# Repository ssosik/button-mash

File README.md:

# whack-a-mole-attack

Project files for a two-player whack-a-mole / button mash game

Original idea by https://github.com/DIYTechBros/ButtonSmack / https://www.youtube.com/watch?v=FXypfZi_UDI

Use a Teensy 4 to control the game, sending serial messages to a Matrix Portal for driving the graphics on a 32x32 LED Panel.

The table was built for a Cub Scout pack and plays as **Cub Scout Button Mash**: a medley of
five short games — whack-a-mole, colour finding, a chase around the ring, a colour puzzle,
and Simon — for one or two players. See [Game modes](#game-modes).

This is the second version of the table. The first ran on a resistor-ladder input, plain
dome lamps and a battery pack; its retrospective is at [the end](#version-1-retrospective).
The firmware still builds for both.

# Components

- [Teensy 4.1](https://www.pjrc.com/store/teensy41.html)
- [32x32 Adafruit LED Matrix](https://www.adafruit.com/product/2026)
- [Adafruit Matrix Portal S3](https://www.adafruit.com/product/5778)
- USB-C power bank + an HUSB238 PD trigger board configured for 5 V
  - Replaces the 2× 21700 pack and the XL4015 buck converter, both now removed from the
    design. The pack ran 8.4 V down to 6.0 V, below the XL4015's 8 V input floor for most
    of a discharge; once the current budget was corrected the table turned out to fit
    inside a 5 V / 3 A PD contract, so the converter went away rather than being worked
    around. [The wiring reference](docs/mole-table-wiring.pdf) records the decision, what
    it costs, and how to reverse it.
- 10 60mm dome push-buttons, each with a 12-pixel WS2812 ring in the cap
- 2 arcade buttons (player start)
- 74AHCT125 level shifter for the pixel data line

# Parts

- 73x100mm PCB strip board
- spade terminals + quick connectors
- wire
- connectors
- 330 Ω resistors (one per cap) and a 1000 µF capacitor
- JST-XH connectors and crimp contacts (parts lists in `docs/`)
- 10K resistors and an M/F barrel connector (version 1 only)
- 2x4s
- 1/2 inch finished plywood
- a few 3D printed pieces

# Layout

```
firmware/WhackAMole/   Teensy 4.1 sketch (Arduino/Teensyduino)
firmware/test/         Host-side tests: every game mode, no Teensy needed
display/               CircuitPython for the Matrix Portal S3, plus a host panel tester
docs/                  Wiring reference (HTML source + PDF), parts lists, doc tooling
hardware/              Button bushings (STL), the WS2812 ring carrier (OpenSCAD),
                       and both PCBs, button board and controller (KiCad, generated
                       from Python)
```

Copying `display/` onto the CIRCUITPY drive is most of it, but not all of it —
see [Flashing the Matrix Portal](#flashing-the-matrix-portal).

# Code

The Teensy owns the game. The Matrix Portal renders whatever it is told and holds no
game state of its own.

| File | Role |
| --- | --- |
| `firmware/WhackAMole/Config.h` | Every pin, timing value, and gameplay tunable. Nothing else holds a bare pin number. |
| `firmware/WhackAMole/Protocol.h` | The controller/display wire protocol. Mirrored by `HANDLERS` in `code.py`. |
| `firmware/WhackAMole/WhackAMole.ino` | Wires the hardware objects together and runs the loop. |
| `firmware/WhackAMole/Game.cpp` | Game states, transitions, and the messages sent for each. Runs the medley. |
| `firmware/WhackAMole/Mode.h` | `MODE_LIST`: every way to play, in order, with its banner and segment length. |
| `firmware/WhackAMole/Dance.cpp` | The splash screen's lamp dance: colours spinning round each ring, all caps flashing, alternate caps swapping. Timing in `Config.h`. |
| `firmware/WhackAMole/*Mode.cpp` | One file per mode: Whack, Captcha, Chase, Logic, Simon. See [Game modes](#game-modes). |
| `firmware/WhackAMole/Player.cpp` | One player's buttons, lamps and score. What a press *means* lives in the modes. |
| `firmware/WhackAMole/ButtonInput.cpp` | Buttons, with debounce and edge detection. Analog ladder or one GPIO per button. |
| `firmware/WhackAMole/Lights.cpp` | Button lamps. Plain on/off or WS2812 pixels. |
| `firmware/WhackAMole/Debug.cpp` | Hardware test screens. See below. |
| `display/code.py` | Listens on the UART and drives the panel. |
| `display/boot.py` | Decides whether the game or the host computer owns writes to CIRCUITPY. |
| `firmware/test/` | Host-side tests that play every mode. `make test`; no Teensy needed. |

Input and lamp hardware are selected at build time in `Config.h`:

```c
#define WAM_INPUT_GPIO    1   // 0 = analog resistor ladder, 1 = one GPIO per button
#define WAM_LIGHTS_PIXELS 1   // 0 = digital dome lamps,     1 = WS2812 in the caps
```

Both default to 1, the current table. For version 1's wiring, override them without
editing the file: `make upload GPIO=0 PIXELS=0`.
CI compiles all four combinations so neither path rots.

# Building

Needs `arduino-cli` with the Teensy core:

```sh
brew install arduino-cli
arduino-cli core install teensy:avr \
  --additional-urls https://www.pjrc.com/teensy/package_teensy_index.json
```

Then:

```sh
make build                    # compile the configuration selected in Config.h
make matrix                   # compile all four input/lamp combinations
make upload                   # compile and flash a connected Teensy
make lint                     # clang-format check + ruff + pin-table check
make test                     # play every game mode on this computer; no Teensy needed
```

# Flashing the Matrix Portal

The Portal runs CircuitPython, so this is three separate things: the interpreter,
one library, and the files in `display/`.

**Unplug the 5 V pigtail from the Portal's USB-C before connecting a computer.**
That port is both its power inlet and its data port, and its screw terminals are fed
from the same node. Adafruit warns that two sources on it at once can damage the board.

## 1. CircuitPython

Double-tap **RESET**; a bootloader drive appears. Drag the UF2 for this board onto it
from [circuitpython.org](https://circuitpython.org/board/adafruit_matrixportal_s3/).
It reboots as `CIRCUITPY`.

`code.py` uses `display.root_group`, so it needs **CircuitPython 9 or later**; 10.x is what it is developed against. Nothing in it
needs porting for 10.

## 2. The one library

`code.py` imports `adafruit_display_text`, which is neither built in nor in this repo.
Everything else it imports — `board`, `busio`, `displayio`, `framebufferio`,
`rgbmatrix`, `terminalio`, `storage`, `digitalio` — is already in the UF2.

```sh
uv tool install circup         # or: pipx install circup
circup install adafruit_display_text
```

A bare `pip install circup` fails on a Homebrew Python with
`externally-managed-environment`. Install it as a *tool*, not into this repo — a
virtualenv created inside `display/` drops a `.gitignore` containing `*`, which
silently hides every file in that directory from git, `code.py` included.

`circup` matches the bundle to the installed CircuitPython. By hand works too: copy
`adafruit_display_text/` out of the bundle for your major version into `CIRCUITPY/lib/`.
A bundle from the wrong major version fails at import with *incompatible .mpy file*.

## 3. The files

Both go in the **root** of `CIRCUITPY`.

```sh
cp display/code.py display/boot.py /Volumes/CIRCUITPY/
```

The splash is drawn in code, so there is no image to copy. A `running-monty-mole.bmp`
left on the drive from an older version is unused and can be deleted.

Copy `boot.py` last. On the next reset it calls `storage.remount("/", readonly=False)`,
which hands writes to the program and makes the drive **read-only to your computer**.
That is the point — it is what lets `highscore.txt` persist — but it does mean you
cannot drag files any more.

**To edit the drive again, hold the UP button while powering on.** If you are already
locked out, Ctrl-C into the REPL and run `import storage; storage.remount("/", readonly=True)`.

## Checking it

On reset, before any serial traffic, `code.py` shows the splash: **CUB SCOUT BUTTON
MASH**, one word at a time in two columns, green for P1 and pink for P2, over a spinning
rainbow pinwheel. That
proves CircuitPython, the library, the HUB75 wiring and the panel, with the Teensy not
involved. The splash gives way as soon as the Teensy sends anything, and
comes back each time the attract loop asks for it. The words, timings, pinwheel and the
small font the title is drawn in (needed because `BUTTON` is too long for the built-in
one) are at the top of `code.py`.

Meanwhile every cap lights white as soon as the Teensy boots, which draws enough to keep a
USB power bank from switching itself off. The caps go dark when the attract loop starts,
and then dance during its splash screen.

The handshake is Teensy-driven: it sends `#CONREADY` and waits in `DisplayReadyWait`,
and the Portal answers `#DSPREADY`. A panel that stays on the splash while the Teensy never advances
is a serial-link fault — check the TX/RX crossover first. Once they are talking, the
debug `DISPLAY` screen sends every protocol message in turn.

## When the panel itself is wrong

`display/panel-test.py` runs on the host, not the board, and drives the panel
directly over the CircuitPython REPL — one pattern at a time, naming each one and
then waiting for you, so what is on the panel and what is on screen cannot drift
apart. Each step states what you should see and what a deviation means.

```sh
python3 display/panel-test.py                # step through all fourteen
python3 display/panel-test.py --hold green   # hold one, hands free for probing
python3 display/panel-test.py --list         # names for --hold / --only
```

The order is deliberate: whether the panel blanks on command at all, then which
colour channels light at a current too low for the supply to matter, then the same
at full current, then geometry. A fault at a dim step is not a power problem; one
that appears only at full white is.

`--hold` is the one to reach for with a meter or a loose connector — it parks a
pattern indefinitely while you reseat the HUB75 socket or probe the panel's own
power terminals.

It interrupts `code.py` on the way in and soft-reboots on the way out, so the game
comes back by itself. Nothing is written to CIRCUITPY.

# Game modes

A game is a **medley**: every mode runs in turn, both players at once, each for its own
segment, with a banner between them. Score carries across all of them and the higher total
wins. The order and segment lengths are `MODE_LIST` in `Mode.h`; everything each mode does
inside its segment is tuned in `Config.h`.

| Mode | Banner | What you do |
| --- | --- | --- |
| Whack | `WHACK` | The original game. One cap blinks; hit it before it moves on. |
| Captcha | `FIND` | Your score turns a colour. Every cap shows a different colour, reshuffling; press the one that matches. |
| Chase | `CHASE` | Every cap dim white, one magenta runner circling. Hit the cap it's on — or the next one, just before it lands. Speeds up with each hit. |
| Logic | `LOGIC` | Each press steps a cap to its next colour. Get all five to the colour your score is showing. |
| Simon | `SIMON` | Watch the sequence, play it back. Right, and it grows by one; wrong or too slow, and it replays. |

Two things to check on the real table:

- **`kChasePath`** in `Config.h` is the order of the caps around each player's ring. It
  defaults to button-index order; set it to the real clockwise order or the runner will jump
  around rather than circle. The build refuses a list that skips or repeats a cap.
- **Point values are first guesses.** `make test` holds every mode with a wrong button to one
  rule — mashing at random loses points on average — but how the modes weigh against each
  other needs real players.

Adding a mode is a line in `MODE_LIST` and a class in `Mode.h`. Forgetting the class is a
compile error, and `make test` fails if its banner won't fit on the panel unscrolled.

# Debug mode

Hold **both start buttons together for two seconds** during the attract loop. Everything
reports to USB serial and mirrors a short banner onto the LED matrix, so the table can be
tested standing up with nothing plugged into it.

A lone start press waits `kStartArbitrationMs` (300 ms) before it starts a game, so the
second button has time to arrive. Without that the first press leaves attract mode
immediately and this gesture can never complete — which is exactly what happened once the
Matrix Portal began answering the handshake and the Teensy stopped sitting in
`DisplayReadyWait`, where nothing competes for the press.

- **P1 start** — next screen
- **P2 start** — act within the current screen
- **both held** — leave debug mode

| Screen | What it is for |
| --- | --- |
| LED WALK | Lights each cap in turn and names it. A cap that stays dark is a wiring fault. |
| LED ALL | Everything on solid. Sit here with a meter on the 5 V rail. |
| BUTTONS | The panel shows the held button, still: `P1 B1`–`P1 B5` in wiring order (blue, red, white, green, yellow), `P2 ST` for P2's start, `NONE` when nothing is down. Serial logs live raw values and colour names for both players. |
| CALIBRATE | Walks you through pressing every button, then prints a paste-ready `kLadderThresholds` table and a safe tolerance. Not needed once the buttons are on GPIOs. |
| DISPLAY | Sends every protocol message in turn so `code.py` can be checked against the full vocabulary without playing a round. |

# Circuit

- **[docs/mole-table-wiring.pdf](docs/mole-table-wiring.pdf)** — the full wiring
  reference: power topology and current budget, the controller stripboard, the button
  board, the per-cap connectors, and build order. `docs/wiring.html` is its source;
  `make wiring-pdf` rebuilds it.
- **[hardware/button-board/](hardware/button-board/)** — the button board as a KiCad PCB,
  with its schematic as a [PDF](hardware/button-board/button-board.pdf).

The button board, rendered from the KiCad layout (`make board-render`). Each cap plugs
into one of J1–J10 and each start button into J11 or J12. Power arrives at the J14 screw
terminal, and J13 carries every switch line and the pixel data back to the controller.

- **[hardware/controller-board/](hardware/controller-board/)** — the controller
  stripboard as a PCB: the socketed Teensy, the 74AHCT125, the harness header, the serial
  link to the Portal and the power terminal, with its schematic as a
  [PDF](hardware/controller-board/controller-board.pdf). Generated end to end from a
  netlist that reads `Config.h`; `make controller-board` rebuilds it and holds it to ERC,
  DRC and schematic parity. Not yet fabricated — the stripboard is what is in the table.

## Pin map

Authoritative version is `firmware/WhackAMole/Config.h`; `make check-pins` fails if the
wiring reference disagrees with it.

| Function | Pins |
| --- | --- |
| Display link (Serial1) | 0 (RX), 1 (TX) |
| Reserved for audio | 6, 7, 10, 18, 19, 20, 21, 23 |
| Floating pin, PRNG seed | 17 |
| **Current table** (`WAM_INPUT_GPIO=1`, `WAM_LIGHTS_PIXELS=1`) | |
| Buttons, one GPIO each (B R W G Y, start) | 9, 11, 12, 24, 25, 26 (P1) / 27, 28, 29, 30, 31, 32 (P2) |
| WS2812 data, both players on one chain | 8 |
| **Version 1** (`WAM_INPUT_GPIO=0`, `WAM_LIGHTS_PIXELS=0`) | |
| Analog ladder in | 27 (P1), 38 (P2) |
| Dome lamps | 28–32 (P1), 37–33 (P2) |

The display link was moved off `Serial2`. Pin 7 is `Serial2` RX **and** the I2S data pin
used by both candidate audio designs, so `Serial2` and sound cannot coexist.

# Version 1 retrospective

Written after the first table's first outing. Most of what it asks for is what version 2
became: a 6-pin JST-XH per cap, buttons on their own GPIOs, WS2812 rings in the caps, and
a USB-C power bank in place of the batteries and buck converter.

## What worked well

- The Teensy is an awesome little computer. Easy to code, super fast, really stable, and overall just worked all the time
- Using switches in series with 10K resistors in between is an awesome way to read in multiple distinct user inputs while only using one analog pin
- The serial communication between the teensy and the Portal Matrix worked better than I expected and was more than fast enough
- The physical dome buttons held up well to an hour of constant abuse from a whole pack of Cub Scouts
- The LED Matrix itself was nice and bright and refreshed quickly
- The 21700 batteries and buck converter worked great to power the whole thing (though
  the pack sat below the converter's rated input floor for most of its discharge — see
  the decision record in the wiring reference)

## What I would do different

- The LEDs on the dome buttons are not great, just not bright. The DIY TechBros design replaced the built-in resistor to improve brightness, but it didn't make much of an improvement for me.
- The wiring scheme I came up with worked but it was ugly. If I were going to rewire this, I'd use a 4-pin JST connector and ribbon cable per LED button. The inline resistors would need to be moved to the perf board.
- The analog ladder is clever but it cannot represent two buttons pressed at once — the
  intermediate voltage decodes as some third button. Since a rewire runs a fresh connector
  to every cap anyway, one more conductor per button buys real simultaneous-press handling
  and retires the threshold table entirely.

## Improvements

- SOUNDS! There is an audio break-out board for the Teensy, adding some sounds would really make the game have an arcade feel
- Better button LEDs. I may try to cram a few WS2812B LEDs into the Dome button housing

## Notes from the rewire

The wiring reference has the details; these are the decisions that shaped it.

- Drive WS2812s with **WS2812Serial**, not Adafruit NeoPixel or FastLED. The bit-banging
  drivers disable interrupts for the length of a frame, which jitters the display link and
  will audibly glitch audio.
- The Teensy 4.1 is 3.3 V logic and WS2812Bs want 0.7×VDD on data. Put a **74AHCT125**
  between the Teensy and the first pixel. This is the usual cause of flaky NeoPixel builds.
- A 330 Ω resistor in series with DIN inside **every** cap, so all ten buttons are
  interchangeable, and 1000 µF across the 5 V rail.
- 10 caps × 12-pixel rings = 120 pixels, **~7.2 A** at full white — far past what the
  supply can give. Only two caps are lit during play, but the debug ALL-ON screen is the
  true worst case, so `kPixelBrightness` is capped at 64/255 (~1.8 A). The two start
  buttons have no lamp and are not in the pixel chain.
- Per-cap connector, 6-pin JST-XH: +5 V, GND, DIN, DOUT, SW, SW-GND. Keep the switch return separate
  from the LED return — a ring at full white puts 720 mA down that ground, and sharing it
  offsets the input the Teensy is reading. The start buttons need two conductors only.
- Full topology, current budget and build order: [docs/mole-table-wiring.pdf](docs/mole-table-wiring.pdf).

## Button LED carrier

`hardware/button-led-carrier.scad` — two printed parts that put a 12-pixel WS2812 ring
behind the dome of the stock 60mm button. The ring seat friction-fits into the plunger
cavity; the bore plug replaces the LED holder in the switch bracket and routes the wires
down the hollow stem, so nothing flexes where the spring can reach it. Measurements and
assembly steps are in the file. The `assert`s at the top will refuse to render if your
ring is too tall for the 4mm cavity — measure `ring_height` before printing.

# Table design

From version 1; the playfield and frame carried over unchanged.

I started from the playfield (16x36 inches) and then just built a table from and legs underneath that. I needed to 3d print a few spacer/bushings so that the buttons were snug in the holes I cut (I didn't have a perfectly-sized hole saw). I also 3d printed 21700 battery holders. The battery holders and perf-board are just screwed to the underside with wood screws. The PortalMatrix is piggy-backed onto the back of the LED panel on the 2x10 socket connector. The LED panel is inset into the middle of the playfield; I added supports underneath to keep it flush with the playfield surface. I also added a 3d-printed bezel around the LED panel in an attempt to make it look like a mole hill and to discourage players from bonking it.

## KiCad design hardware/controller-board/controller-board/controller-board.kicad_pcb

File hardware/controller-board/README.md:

# Controller board

The controller stripboard from [the wiring reference](../../docs/mole-table-wiring.pdf)
— 33 cuts and nine jumpers around a socketed Teensy 4.1 — as a two-layer PCB. Same
parts, same connectors, same pinout: the harness to the button board, the serial cable
to the Matrix Portal and the 5 V lead from the star all plug into it unchanged.

## Files

| File | What |
| --- | --- |
| `gen-netlist.py` | The single source of truth. Harness positions come from the button board's generator and switch pins from `Config.h`, so neither can drift from it. |
| `gen-schematic.py` | Draws the schematic from that netlist, and writes the Teensy 4.1 symbol KiCad does not ship. |
| `gen-pcb.py` | Places, routes and pours the board through KiCad's own `pcbnew` API, and writes the Teensy footprint. |
| `controller-board/` | The KiCad project. Everything in it is generated. |
| `controller-board.pdf` | The schematic as a drawing. |

```sh
make controller-board   # regenerate all of it, then ERC, DRC and schematic parity
make board-render       # the 3D view above
```

`gen-pcb.py` has to run under the Python inside KiCad, the only one that can import
`pcbnew`; the Makefile knows where it is. Unlike the button board, nothing here is
laid out by hand, so regenerating is always safe: edit the generator, never the board.

## What it checks

`make controller-board` fails on any of these, warnings included:

- **ERC** — 0 errors, 0 warnings. Every open pin carries an explicit no-connect.
- **DRC** — 0 violations, 0 unconnected items.
- **Schematic parity** — every footprint is linked to its symbol and every pad
  carries the net the schematic gives it. The links are UUIDs derived from
  reference designators, so the two generators agree without sharing state.

The schematic's exported netlist also diffs clean against `gen-netlist.py` — 18 nets,
53 nodes — and the netlist validator refuses a pin on two nets, a pin on none, a net
with one end, or a disabled '125 output wired to anything.

## Layout

It copies the stripboard on purpose. The harness header sits one column from the
Teensy's left row, so twelve of its fourteen positions are a straight trace to the
Teensy pin opposite — the PCB version of "the strip is the wire". The other two arrive
from elsewhere, exactly as on the stripboard: position 2 is ground, from the pour, and
position 5 is the level-shifted pixel data, run down the board's left edge on the
bottom layer.

| Ref | Part | Notes |
| --- | --- | --- |
| U1 | Teensy 4.1 on two 1×24 female headers | **Cut the VIN–VUSB pad** on the Teensy, or USB and the star will fight. |
| U2 | 74AHCT125 in a DIP-14 socket | Gate 1 lifts pin 8 to 5 V. Gates 2–4 are disabled (OE high), inputs grounded. |
| J1 | 1×14 2.54 mm pin header | Takes the harness's socket end; mates with button board J13. Pin 1 is P1 BLUE. |
| J2 | B3B-XH-A | Serial1 to the Portal: 1 GND, 2 Teensy RX, 3 Teensy TX. The cable crosses 2 and 3. |
| J3 | MX126 screw terminal | +5 V and GND from the star. A screw terminal, as on the button board. |
| C1 | 100 µF / 16 V | Bulk at the power entry. Stripe to GND. |
| C2 | 100 nF ceramic | Decoupling, straight onto the '125's VCC pin. |
| H1–H4 | M3, unplated | Mounting. |

Ground is a pour on both layers. +5 V reaches VIN and C1 on the top layer, and runs
along the top edge on the bottom layer to the '125.

## Before ordering

This has been through every check KiCad offers, but not through a fab or a first
article. Open it in KiCad and look it over before you send it anywhere, and check
the Teensy footprint against a real Teensy and its headers — it is drawn from the
published 0.6" row spacing, not measured from a part.

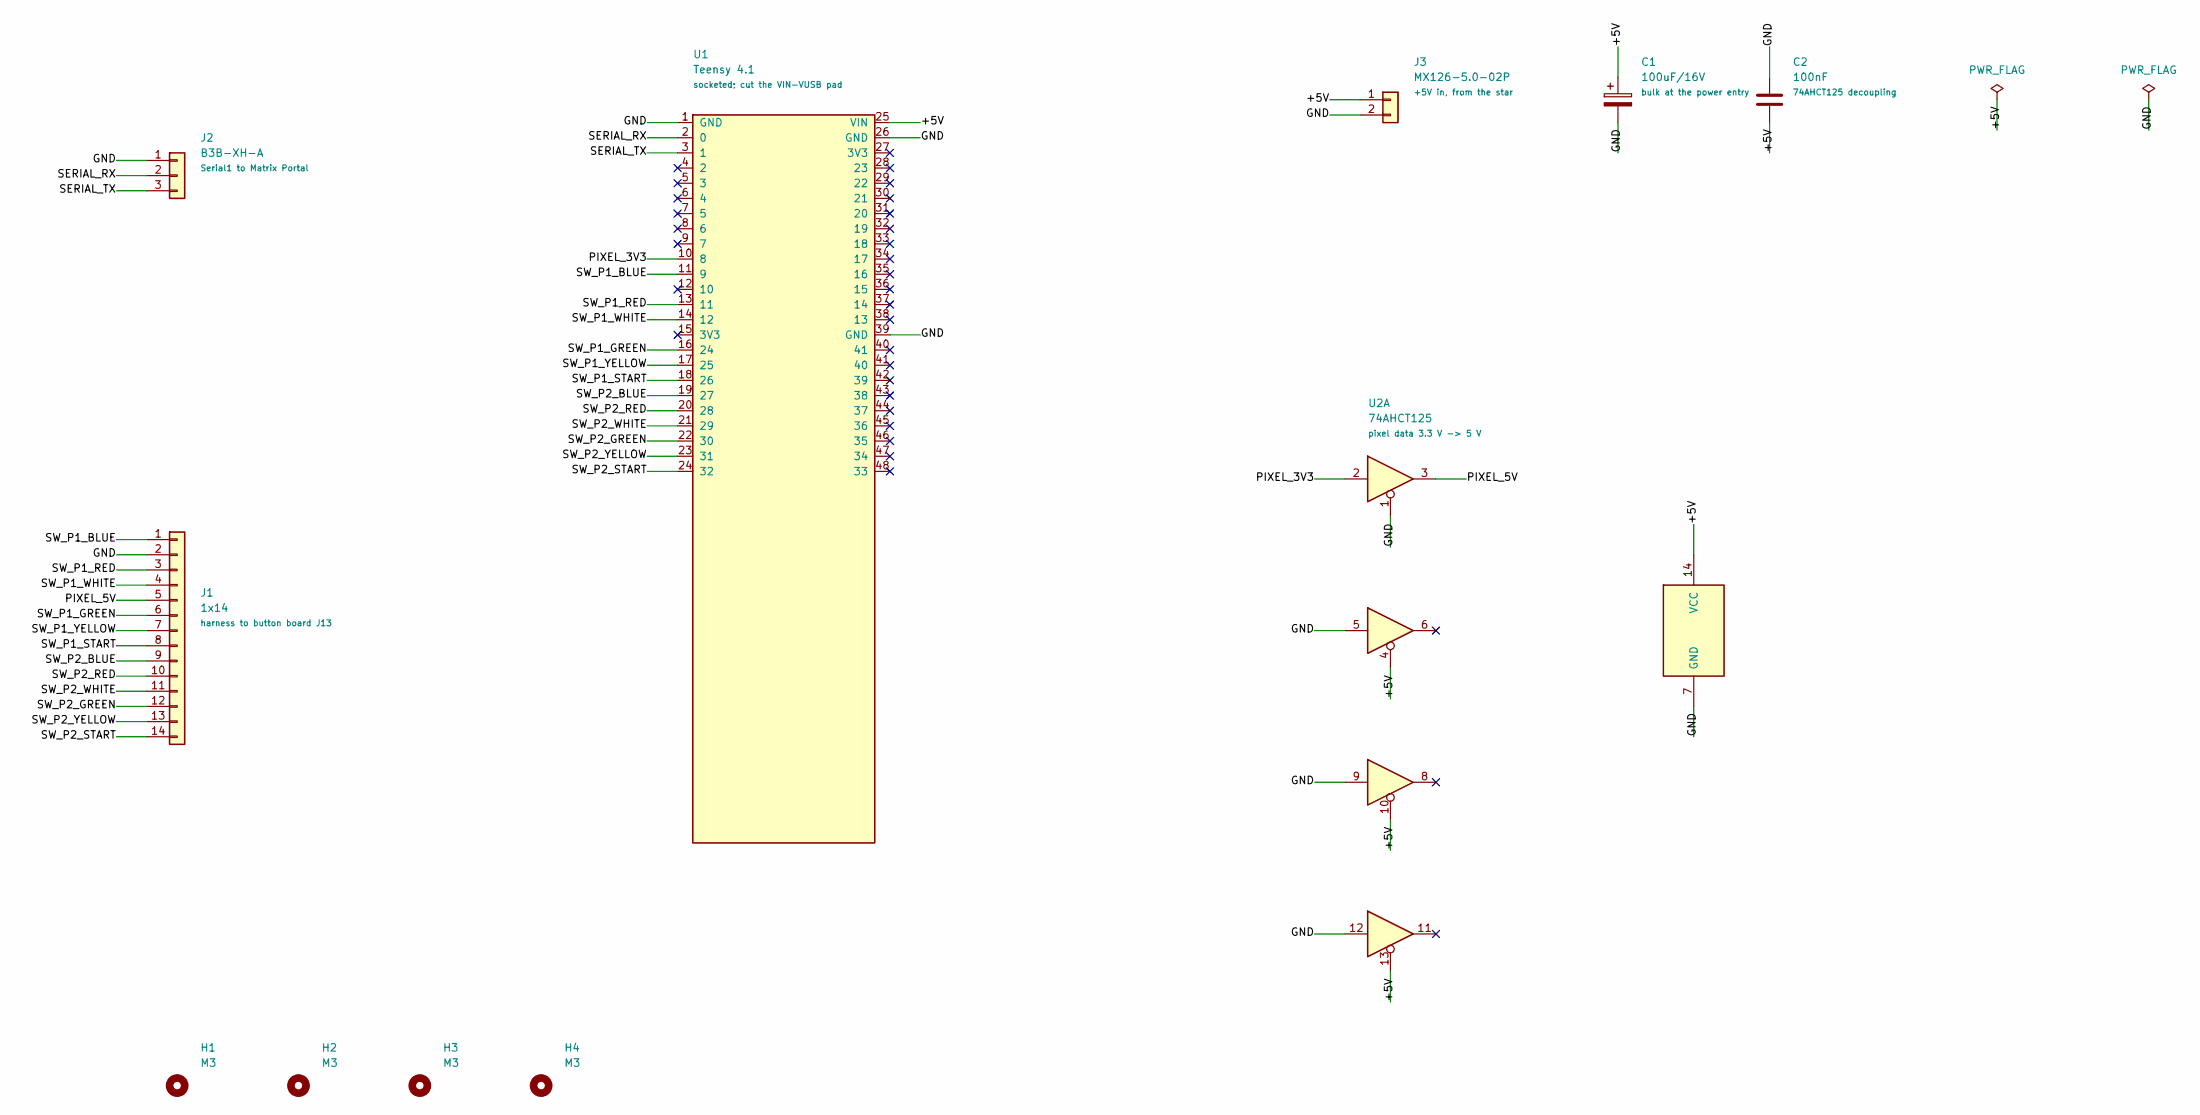
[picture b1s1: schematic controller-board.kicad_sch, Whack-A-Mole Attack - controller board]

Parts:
C1: 100uF/16V; CP_Radial_D6.3mm_P2.50mm
C2: 100nF; C_Disc_D5.0mm_W2.5mm_P5.00mm
H1, H2, H3, H4: M3; MountingHole_3.2mm_M3
J1: 1x14; PinHeader_1x14_P2.54mm_Vertical
J2: B3B-XH-A; JST_XH_B3B-XH-A_1x03_P2.50mm_Vertical
J3: MX126-5.0-02P; TerminalBlock_MaiXu_MX126-5.0-02P_1x02_P5.00mm
U1: Teensy 4.1; Teensy41_Socketed
U2: 74AHCT125; DIP-14_W7.62mm_Socket

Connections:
/+5V: C1.1, C2.2, J3.1, U1.25 (VIN), U2.4, U2.10, U2.13, U2.14 (VCC)
/GND: C1.2, C2.1, J1.2, J2.1, J3.2, U1.1 (GND), U1.26 (GND), U1.39 (GND), U2.1, U2.5, U2.7 (GND), U2.9, U2.12
/PIXEL_3V3: U1.10 (8), U2.2
/PIXEL_5V: J1.5, U2.3
/SERIAL_RX: J2.2, U1.2 (0)
/SERIAL_TX: J2.3, U1.3 (1)
/SW_P1_BLUE: J1.1, U1.11 (9)
/SW_P1_GREEN: J1.6, U1.16 (24)
/SW_P1_RED: J1.3, U1.13 (11)
/SW_P1_START: J1.8, U1.18 (26)
/SW_P1_WHITE: J1.4, U1.14 (12)
/SW_P1_YELLOW: J1.7, U1.17 (25)
/SW_P2_BLUE: J1.9, U1.19 (27)
/SW_P2_GREEN: J1.12, U1.22 (30)
/SW_P2_RED: J1.10, U1.20 (28)
/SW_P2_START: J1.14, U1.24 (32)
/SW_P2_WHITE: J1.11, U1.21 (29)
/SW_P2_YELLOW: J1.13, U1.23 (31)

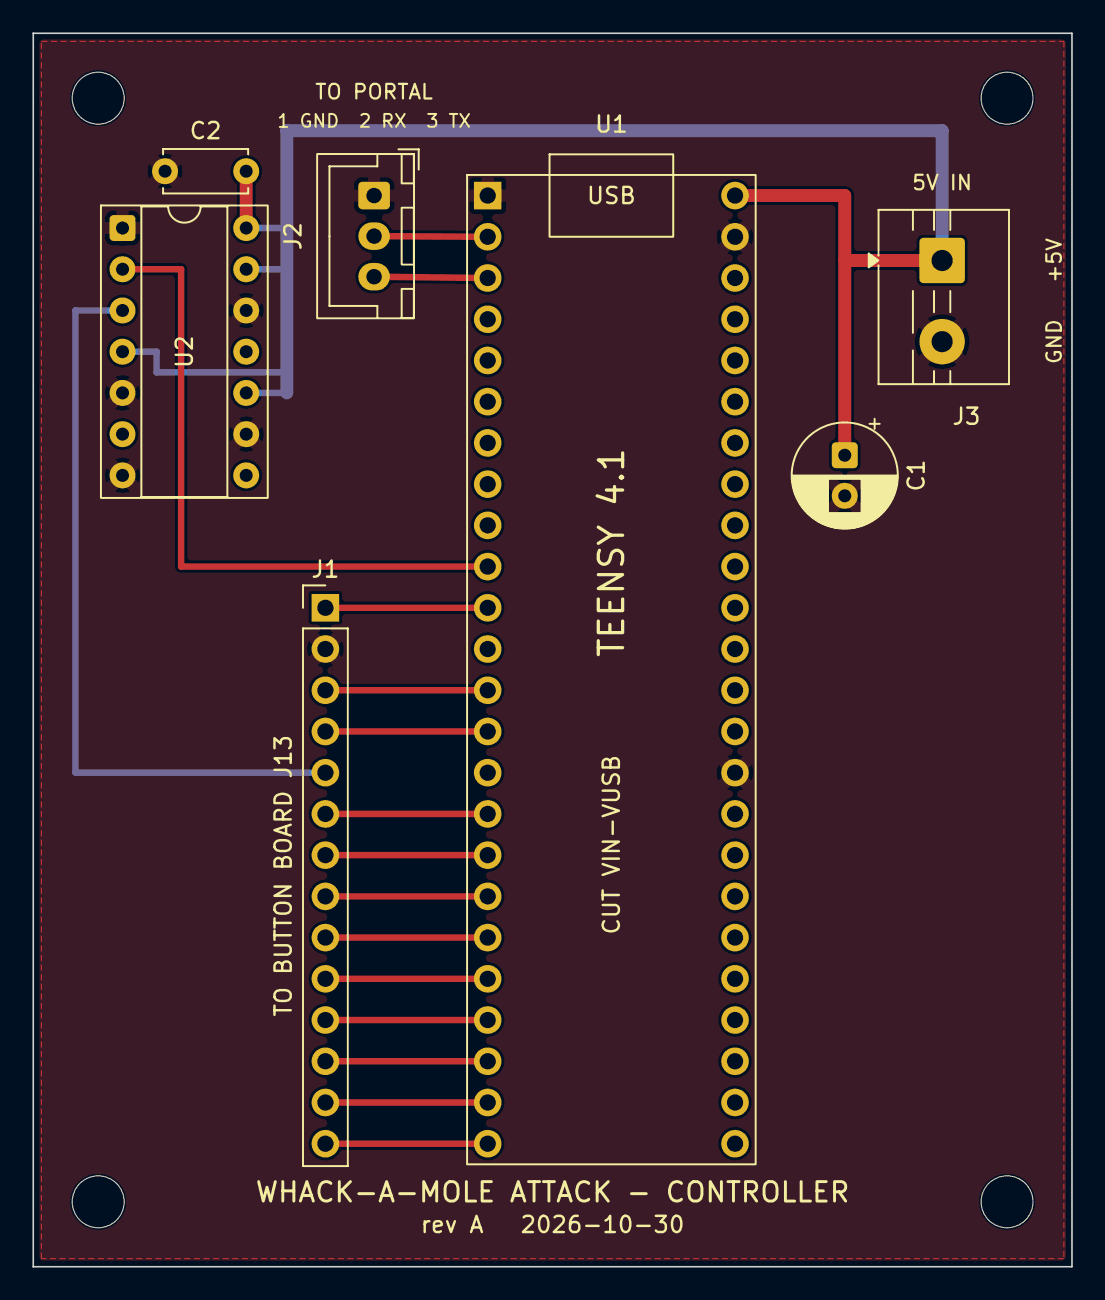
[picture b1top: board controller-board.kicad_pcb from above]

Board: 2 copper layers, 64.0 x 76.0 mm, 11 parts (0 on the bottom side), 18 nets.

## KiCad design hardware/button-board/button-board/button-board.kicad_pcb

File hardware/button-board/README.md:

# Button board

Twelve connectors, three power nets, one daisy chain. The stripboard version is
documented in [the wiring reference](../../docs/mole-table-wiring.pdf) — 63 cuts
and 31 hand-soldered wires. This directory is the PCB alternative.

## Files

| File | What |
| --- | --- |
| `gen-netlist.py` | The single source of truth. Everything else derives from it. |
| `gen-schematic.py` | Draws the schematic from that netlist. |
| `button-board/` | The KiCad project. `button-board.net` and `button-board.kicad_sch` in it are generated; `button-board.kicad_pcb` is laid out by hand. |
| `button-board.pdf` | The schematic as a drawing, for reading away from KiCad. |

```sh
cd hardware/button-board
python3 gen-netlist.py                               # readable net table
python3 gen-netlist.py --kicad > button-board/button-board.net
python3 gen-schematic.py       > button-board/button-board.kicad_sch

# Regenerating the schematic assigns fresh symbol UUIDs, so the board's
# footprint links go stale. Re-import with "Update PCB from Schematic" and
# tick "Re-link footprints to schematic symbols based on their reference
# designators", or the 20 existing footprints come back as orphans.
```

Connections are made with net labels on pin stubs rather than drawn wires. For
twelve connectors and three buses that is the clearer drawing, and it removes
the class of bug where a generated wire lands a fraction off a pin and silently
connects nothing.

Both outputs are checked, not assumed. ERC reports **0 errors, 0 warnings**, and
the schematic is exported back to a netlist and diffed against the hand-built
one — 25 nets and 83 nodes, matching exactly. ERC alone is not sufficient: an
earlier draft passed ERC while connecting nothing at all.

Ribbon positions are read out of `firmware/WhackAMole/Config.h` rather than
written down here, so the netlist cannot drift from the firmware the way the
documentation did three times. The generator also refuses to emit anything if a
connector pin lands on two nets, on none, or does not exist — verified against
injected faults, not only on correct input.

## Designators

`J1`–`J10` are the lit caps **in pixel-chain order**: P1 blue, red, white,
green, yellow, then P2 in the same sequence. That is both the order data flows
and the order `Config.h` addresses them, so the reference designator is the
pixel index. `J11`/`J12` are the start buttons, `J13` the ribbon to the
controller, `J14` power in from the HUSB238.

## The one thing layout must get right

`GND_LED` and `GND_SW` are **separate nets joined only at `NT1`**. That single
point is the star. A ground pour that merges them anywhere else puts up to
1.81 A of ring current through the switch reference, and the symptom is inputs
that misread while the LEDs are busy — intermittent, load-dependent, and
unpleasant to chase. Keep the net tie, and check it survives the pour.

Beyond that: `+5V` and `GND_LED` want wide copper, since they carry the ring
current. Everything else is signal.

## Footprints

Checked against KiCad 10's libraries. Verify them if you are on another release
— JST and pin header library names have moved between versions.

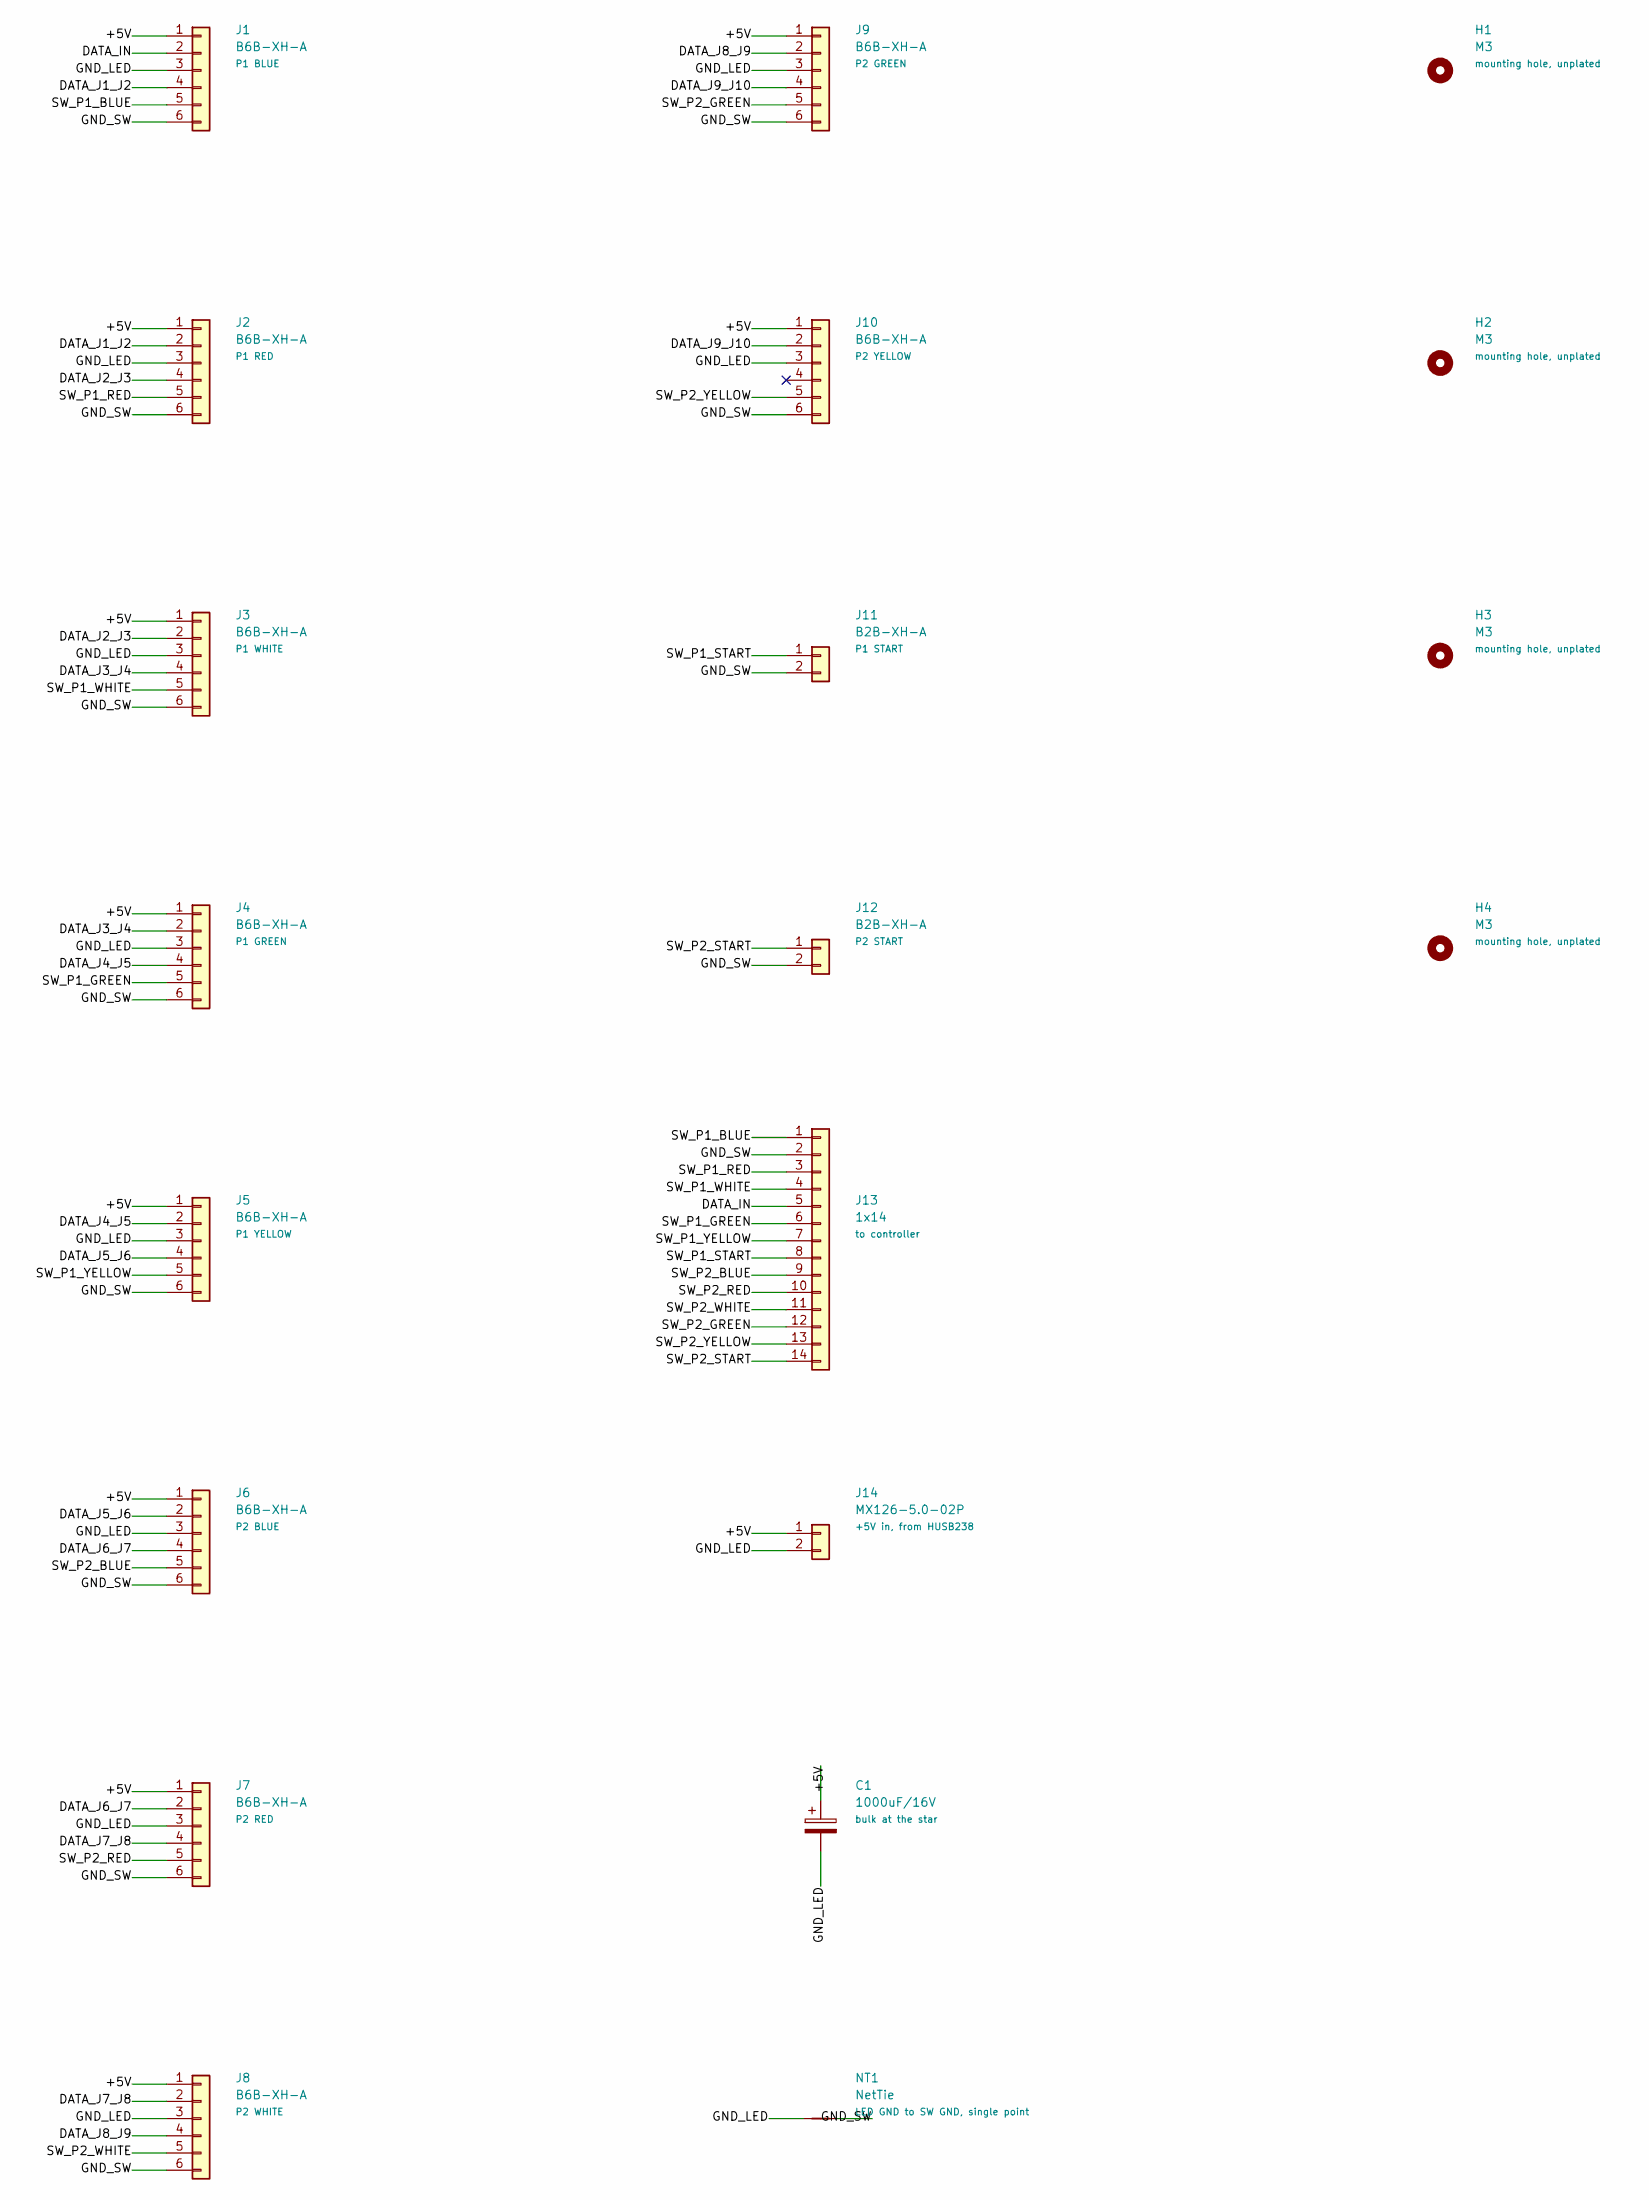
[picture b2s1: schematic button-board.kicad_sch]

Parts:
C1: 1000uF/16V; CP_Radial_D10.0mm_P5.00mm
H1, H2, H3, H4: M3; MountingHole_3.2mm_M3
J1, J2, J3, J4, J5, J6, J7, J8, J9, J10: B6B-XH-A; JST_XH_B6B-XH-A_1x06_P2.50mm_Vertical
J11, J12: B2B-XH-A; JST_XH_B2B-XH-A_1x02_P2.50mm_Vertical
J13: 1x14; JST_XH_B14B-XH-A_1x14_P2.50mm_Vertical
J14: MX126-5.0-02P; TerminalBlock_MaiXu_MX126-5.0-02P_1x02_P5.00mm
NT1: NetTie; NetTie-2_THT_Pad1.0mm

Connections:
/+5V: C1.1, J1.1, J2.1, J3.1, J4.1, J5.1, J6.1, J7.1, J8.1, J9.1, J10.1, J14.1
/DATA_IN: J1.2, J13.5
/DATA_J1_J2: J1.4, J2.2
/DATA_J2_J3: J2.4, J3.2
/DATA_J3_J4: J3.4, J4.2
/DATA_J4_J5: J4.4, J5.2
/DATA_J5_J6: J5.4, J6.2
/DATA_J6_J7: J6.4, J7.2
/DATA_J7_J8: J7.4, J8.2
/DATA_J8_J9: J8.4, J9.2
/DATA_J9_J10: J9.4, J10.2
/GND_LED: C1.2, J1.3, J2.3, J3.3, J4.3, J5.3, J6.3, J7.3, J8.3, J9.3, J10.3, J14.2, NT1.1
/GND_SW: J1.6, J2.6, J3.6, J4.6, J5.6, J6.6, J7.6, J8.6, J9.6, J10.6, J11.2, J12.2, J13.2, NT1.2
/SW_P1_BLUE: J1.5, J13.1
/SW_P1_GREEN: J4.5, J13.6
/SW_P1_RED: J2.5, J13.3
/SW_P1_START: J11.1, J13.8
/SW_P1_WHITE: J3.5, J13.4
/SW_P1_YELLOW: J5.5, J13.7
/SW_P2_BLUE: J6.5, J13.9
/SW_P2_GREEN: J9.5, J13.12
/SW_P2_RED: J7.5, J13.10
/SW_P2_START: J12.1, J13.14
/SW_P2_WHITE: J8.5, J13.11
/SW_P2_YELLOW: J10.5, J13.13

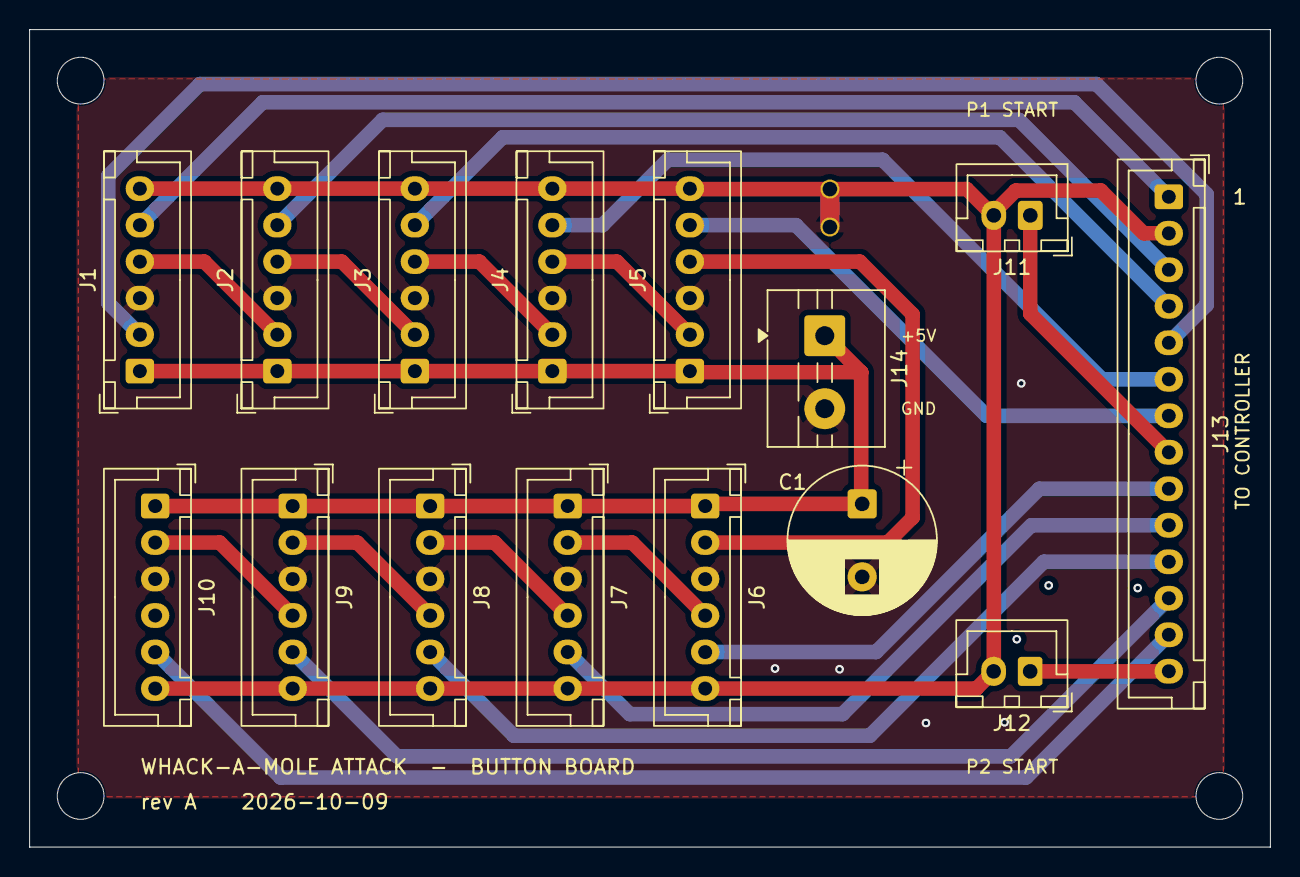
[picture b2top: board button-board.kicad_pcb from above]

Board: 2 copper layers, 85.0 x 56.0 mm, 20 parts (0 on the bottom side), 25 nets.

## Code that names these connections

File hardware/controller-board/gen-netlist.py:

#!/usr/bin/env python3
"""The controller board's netlist: one description the schematic and the PCB
are both generated from, so the two cannot disagree.

It is the stripboard in docs/wiring.html, made as a PCB: a socketed Teensy
4.1, a 74AHCT125 lifting the pixel data to 5 V, the 14-way header for the
harness to the button board, a 3-pin JST-XH serial link to the Matrix Portal,
and a screw terminal for 5 V in from the star.

Nothing here is written down twice. The harness positions come from the
button board's own generator, so both ends of the harness agree by
construction, and the switch pins come from Config.h, so a firmware pin change
that the board does not follow fails here instead of on the table.

    python3 hardware/controller-board/gen-netlist.py    # readable net table
"""

import importlib.util
import pathlib
import sys
from collections import defaultdict

HERE = pathlib.Path(__file__).resolve().parent
_spec = importlib.util.spec_from_file_location(
    "button_netlist", HERE.parent / "button-board" / "gen-netlist.py"
)
BB = importlib.util.module_from_spec(_spec)
_spec.loader.exec_module(BB)

# The Teensy 4.1's two outer pin rows, top view, USB end first. Pads are
# numbered 1-24 down the left row and 25-48 down the right, so pad numbers
# read the way the board is held rather than anticlockwise like a DIP.
TEENSY_LEFT = [
    "GND",
    "0",
    "1",
    "2",
    "3",
    "4",
    "5",
    "6",
    "7",
    "8",
    "9",
    "10",
    "11",
    "12",
    "3V3",
    "24",
    "25",
    "26",
    "27",
    "28",
    "29",
    "30",
    "31",
    "32",
]
TEENSY_RIGHT = [
    "VIN",
    "GND",
    "3V3",
    "23",
    "22",
    "21",
    "20",
    "19",
    "18",
    "17",
    "16",
    "15",
    "14",
    "13",
    "GND",
    "41",
    "40",
    "39",
    "38",
    "37",
    "36",
    "35",
    "34",
    "33",
]
TEENSY_PINS = TEENSY_LEFT + TEENSY_RIGHT


def teensy_pad(label, nth=0):
    """Pad number of a Teensy pin by its silkscreen label (nth for GND, 3V3)."""
    pads = [i + 1 for i, name in enumerate(TEENSY_PINS) if name == str(label)]
    return pads[nth]


PIXEL_PIN = 8  # kPixelDataPin; Serial2 TX, which WS2812Serial drives
SERIAL_RX, SERIAL_TX = 0, 1  # Serial1, to the Matrix Portal

FP_TEENSY = "controller-board:Teensy41_Socketed"
FP_SHIFTER = "Package_DIP:DIP-14_W7.62mm_Socket"
FP_HARNESS = "Connector_PinHeader_2.54mm:PinHeader_1x14_P2.54mm_Vertical"
FP_SERIAL = "Connector_JST:JST_XH_B3B-XH-A_1x03_P2.50mm_Vertical"
# A screw terminal, as on the button board: nothing else on this board is
# 2-pin, but there is no reason to let a power lead be pluggable anywhere.
FP_PWR = "TerminalBlock:TerminalBlock_MaiXu_MX126-5.0-02P_1x02_P5.00mm"
FP_BULK = "Capacitor_THT:CP_Radial_D6.3mm_P2.50mm"
FP_DECOUPLE = "Capacitor_THT:C_Disc_D5.0mm_W2.5mm_P5.00mm"
FP_HOLE = "MountingHole:MountingHole_3.2mm_M3"

U1, U2, J1, J2, J3, C1, C2 = "U1", "U2", "J1", "J2", "J3", "C1", "C2"
HOLES = ["H1", "H2", "H3", "H4"]

# 74AHCT125 (74LS125 pinout). Gate 1 carries the pixel data; gates 2-4 are
# disabled (OE high) with their inputs held low so nothing floats.
SHIFTER = {
    "1OE": 1, "1A": 2, "1Y": 3, "2OE": 4, "2A": 5, "2Y": 6, "GND": 7,
    "3Y": 8, "3A": 9, "3OE": 10, "4Y": 11, "4A": 12, "4OE": 13, "VCC": 14,
}  # fmt: skip
SHIFTER_OPEN = ["2Y", "3Y", "4Y"]

# The serial header, pin for pin as the stripboard's: ground, then the
# Teensy's RX, then its TX. The cable crosses them over to the Portal.
SERIAL_PINS = {1: "GND", 2: "SERIAL_RX", 3: "SERIAL_TX"}


def harness_teensy_pin(pos):
    """What a harness position carries at this end: a Teensy pin, or a net."""
    pin = BB.RIBBON_TEENSY[pos - 1]
    if pin == 10:
        return "GND"  # audio-reserved pin 10's position, reused for ground
    if pin == "3V3":
        return "PIXEL_5V"  # 3.3 V's position, reused for the shifted data
    return pin


def switch_names():
    """Teensy pin -> switch net name, named as the button board names them."""
    p1, p2 = BB.config_pins()
    names = {}
    for player, pins in (("P1", p1), ("P2", p2)):
        for colour, pin in zip(BB.CAP_COLOURS + ["START"], pins):
            names[pin] = f"SW_{player}_{colour}"
    return names


def build():
    """Return (components, nets): components as (ref, value, footprint, note)."""
    comps = [
        (U1, "Teensy 4.1", FP_TEENSY, "socketed; cut the VIN-VUSB pad"),
        (U2, "74AHCT125", FP_SHIFTER, "pixel data 3.3 V -> 5 V"),
        (J1, "1x14", FP_HARNESS, "harness to button board J13"),
        (J2, "B3B-XH-A", FP_SERIAL, "Serial1 to Matrix Portal"),
        (J3, "MX126-5.0-02P", FP_PWR, "+5V in, from the star"),
        (C1, "100uF/16V", FP_BULK, "bulk at the power entry"),
        (C2, "100nF", FP_DECOUPLE, "74AHCT125 decoupling"),
    ]
    comps += [(ref, "M3", FP_HOLE, "mounting hole, unplated") for ref in HOLES]

    nets = defaultdict(list)
    nets["+5V"] += [(J3, 1), (U1, teensy_pad("VIN")), (C1, 1), (C2, 2)]
    nets["+5V"] += [(U2, SHIFTER[p]) for p in ("VCC", "2OE", "3OE", "4OE")]
    nets["GND"] += [(J3, 2), (C1, 2), (C2, 1), (J2, 1)]
    nets["GND"] += [(U1, teensy_pad("GND", n)) for n in range(3)]
    nets["GND"] += [(U2, SHIFTER[p]) for p in ("GND", "1OE", "2A", "3A", "4A")]

    nets["PIXEL_3V3"] = [(U1, teensy_pad(PIXEL_PIN)), (U2, SHIFTER["1A"])]
    nets["PIXEL_5V"] = [(U2, SHIFTER["1Y"])]
    nets["SERIAL_RX"] = [(J2, 2), (U1, teensy_pad(SERIAL_RX))]
    nets["SERIAL_TX"] = [(J2, 3), (U1, teensy_pad(SERIAL_TX))]

    names = switch_names()
    for pos in range(1, 15):
        carries = harness_teensy_pin(pos)
        if isinstance(carries, str):
            nets[carries].append((J1, pos))
        elif carries in names:
            nets[names[carries]] = [(J1, pos), (U1, teensy_pad(carries))]
        else:
            sys.exit(f"harness position {pos} lands on Teensy pin {carries}, no button")
    return comps, dict(nets)


def validate(comps, nets):
    """Every connector pin on exactly one net; every net with two ends."""
    expect = {J1: set(range(1, 15)), J2: {1, 2, 3}, J3: {1, 2}, C1: {1, 2}, C2: {1, 2}}
    expect[U2] = {n for p, n in SHIFTER.items() if p not in SHIFTER_OPEN}
    seen = defaultdict(list)
    for nodes in nets.values():
        for ref, pin in nodes:
            seen[ref].append(pin)
    problems = []
    for ref, pins in expect.items():
        got = seen[ref]
        dupes = sorted({p for p in got if got.count(p) > 1})
        if dupes:
            problems.append(f"{ref}: pin(s) {dupes} on more than one net")
        if pins - set(got):
            problems.append(f"{ref}: pin(s) {sorted(pins - set(got))} on no net")
        if set(got) - pins:
            problems.append(f"{ref}: pin(s) {sorted(set(got) - pins)} should be open")
    teensy = seen[U1]
    if len(teensy) != len(set(teensy)):
        problems.append("U1: a Teensy pad is on more than one net")
    for name, nodes in nets.items():
        if len(nodes) < 2:
            problems.append(f"net {name} has only {len(nodes)} node")
    return problems


def table(comps, nets):
    out = ["COMPONENTS", "-" * 72]
    for ref, val, fp, note in comps:
        out.append(f"{ref:<4} {val:<14} {note}")
        out.append(f"     {fp}")
    out += ["", f"NETS ({len(nets)})", "-" * 72]
    for name in sorted(nets, key=lambda n: (n not in ("+5V", "GND"), n)):
        nodes = []
        for ref, pin in nets[name]:
            label = f"[{TEENSY_PINS[pin - 1]}]" if ref == U1 else ""
            nodes.append(f"{ref}.{pin}{label}")
        out.append(f"{name:<16} {', '.join(nodes)}")
    return "\n".join(out)


def main():
    comps, nets = build()
    problems = validate(comps, nets)
    if problems:
        print("netlist is inconsistent:", file=sys.stderr)
        for p in problems:
            print("  " + p, file=sys.stderr)
        return 1
    print(table(comps, nets))
    return 0


if __name__ == "__main__":
    sys.exit(main())
